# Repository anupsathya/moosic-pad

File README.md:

# moo-sic pad

A simple macro pad with 4 Cherry MX keys, a PEC-11R Rotary Encoder, a mini OLED screen and a vibration motor.

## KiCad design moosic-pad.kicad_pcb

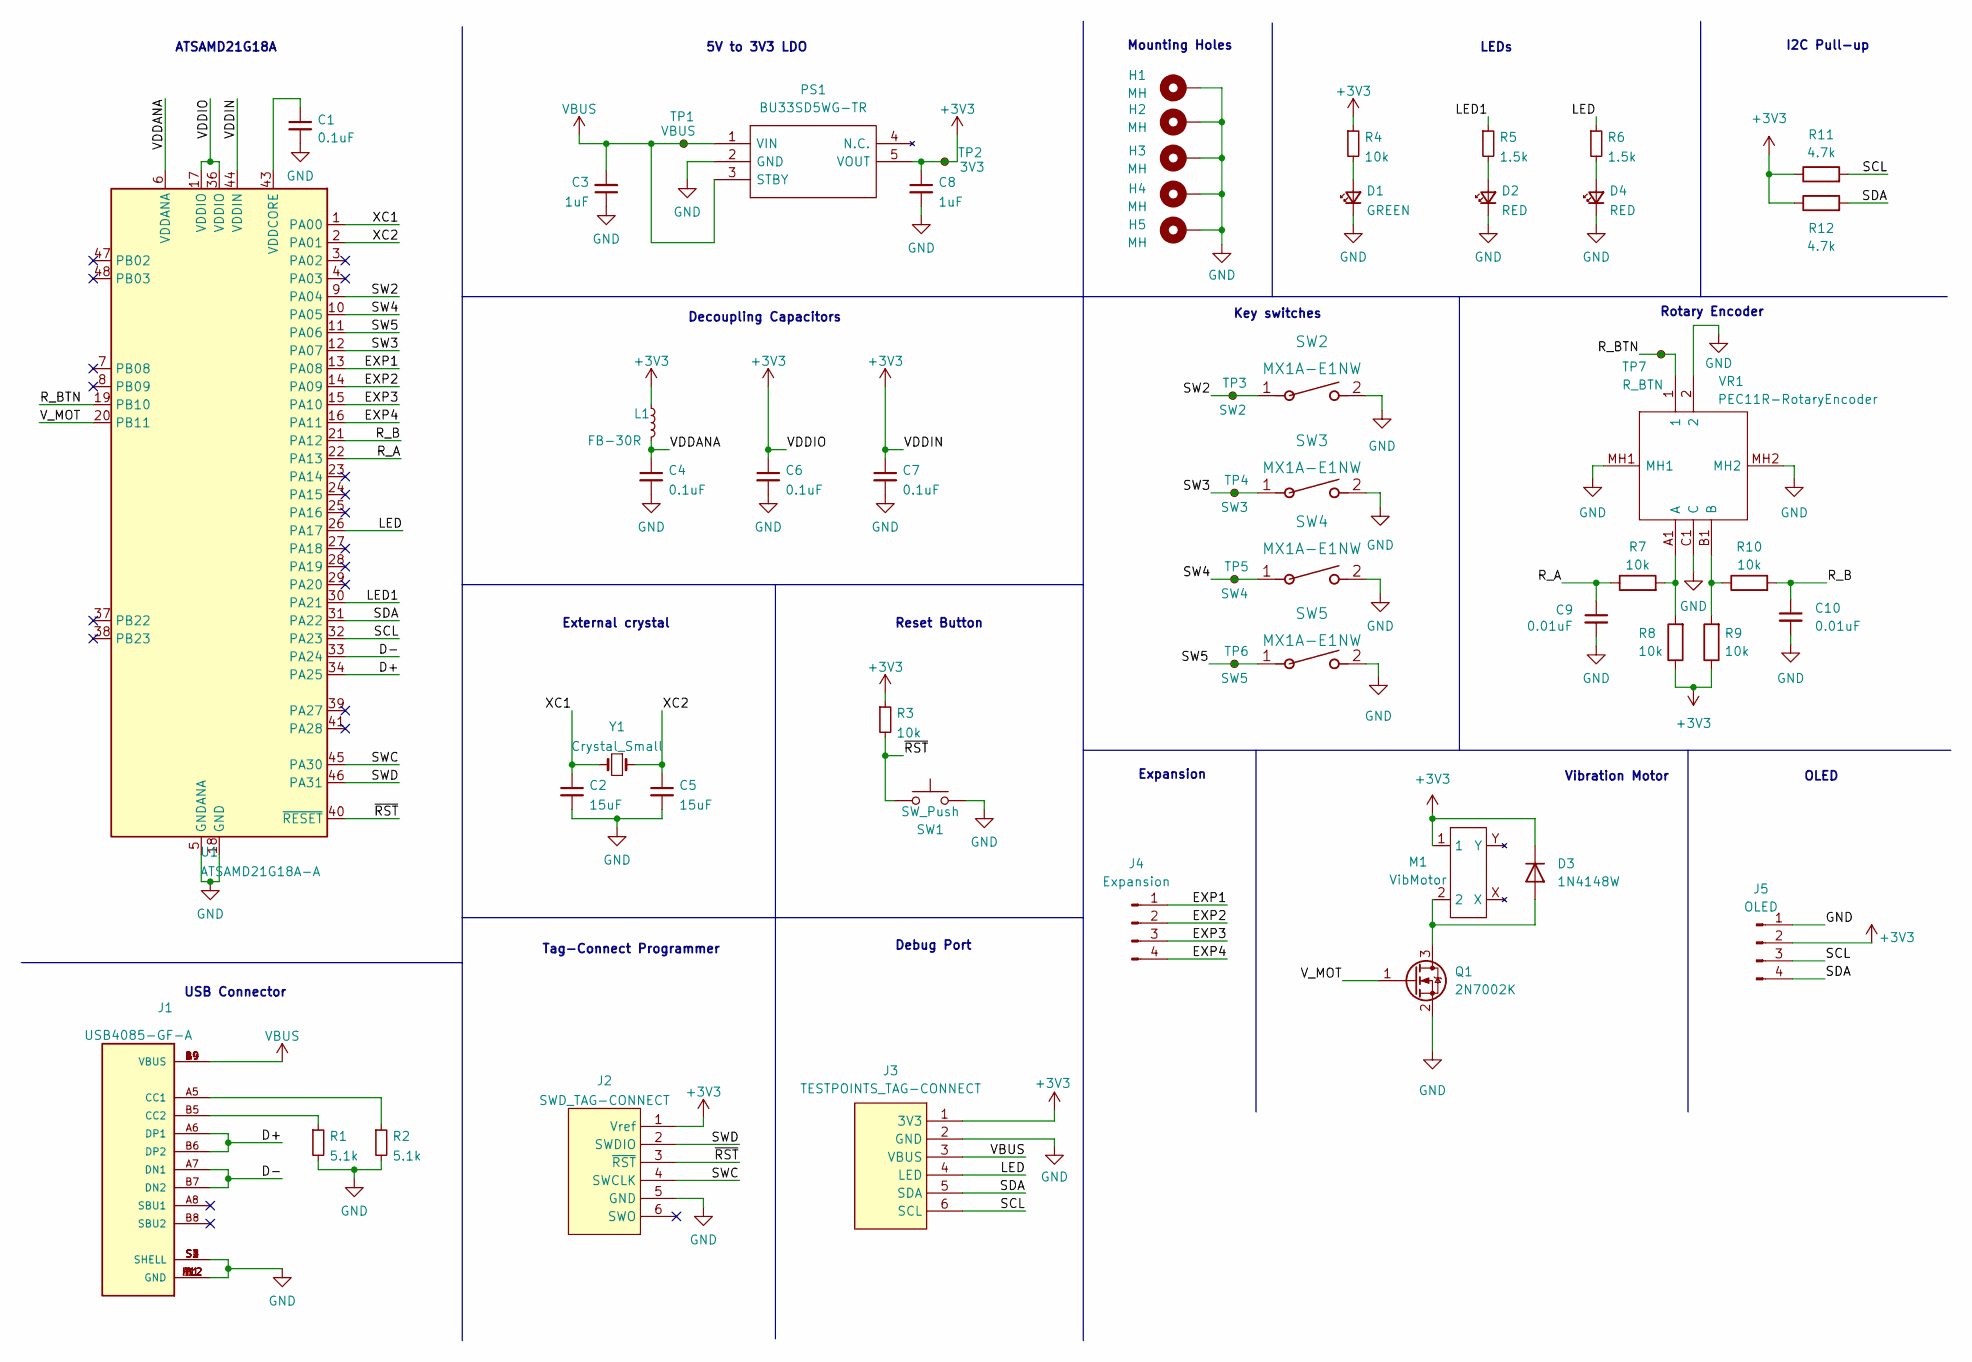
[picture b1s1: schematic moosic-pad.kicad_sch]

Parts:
C1, C4, C6, C7: 0.1uF; C_0603_1608Metric_Pad1.08x0.95mm_HandSolder
C2, C5: 15uF; C_0603_1608Metric_Pad1.08x0.95mm_HandSolder
C3, C8: 1uF; C_0603_1608Metric_Pad1.08x0.95mm_HandSolder
C9, C10: 0.01uF; C_0603_1608Metric_Pad1.08x0.95mm_HandSolder
D1: GREEN; LED_0603_1608Metric
D2, D4: RED; LED_0603_1608Metric
D3: 1N4148W; D_SOD-123
H1, H2, H3, H4, H5: MH; MountingHole_2.7mm_M2.5_DIN965_Pad
J1: USB4085-GF-A; GCT_USB4085-GF-A; PARTREV A4
J2: SWD_TAG-CONNECT; Tag-Connect_TC2030-IDC-FP_2x03_P1.27mm_Vertical
J3: TESTPOINTS_TAG-CONNECT; Tag-Connect_TC2030-IDC-NL_2x03_P1.27mm_Vertical
J4: Expansion; PinHeader_1x04_P1.00mm_Vertical
J5: OLED; PinHeader_1x04_P2.54mm_Vertical
L1: FB-30R; L_0603_1608Metric
M1: VibMotor; SeeedStudio_VibMotor
PS1: BU33SD5WG-TR; SOT95P280X125-5N; Mouser Part Number 755-BU33SD5WG-TR
Q1: 2N7002K; SOT-23
R1, R2: 5.1k; R_0603_1608Metric_Pad0.98x0.95mm_HandSolder
R3, R4, R7, R8, R9, R10: 10k; R_0603_1608Metric_Pad0.98x0.95mm_HandSolder
R5, R6: 1.5k; R_0603_1608Metric_Pad0.98x0.95mm_HandSolder
R11, R12: 4.7k; R_0603_1608Metric_Pad0.98x0.95mm_HandSolder
SW1: SW_Push; SW_SPST_TL3305A
SW2, SW3, SW4, SW5: MX1A-E1NW
TP1: VBUS; TestPoint_Pad_D1.0mm
TP2: 3V3; TestPoint_Pad_D1.0mm
TP3: SW2; TestPoint_Pad_D1.0mm
TP4: SW3; TestPoint_Pad_D1.0mm
TP5: SW4; TestPoint_Pad_D1.0mm
TP6: SW5; TestPoint_Pad_D1.0mm
TP7: R_BTN; TestPoint_Pad_D1.0mm
U1: ATSAMD21G18A-A; TQFP-48_7x7mm_P0.5mm
VR1: PEC11R-RotaryEncoder; PEC11R4220FS0024; Mouser Part Number 652-PEC11R-4220F-S24
Y1: Crystal_Small; Crystal_SMD_3215-2Pin_3.2x1.5mm

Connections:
+3V3: C6.1, C7.1, C8.1, D3.1 (K), J2.1 (Vref), J3.1 (3V3), J5.2, L1.1, M1.1, PS1.5 (VOUT), R3.1, R4.1, R8.1, R9.1, R11.1, R12.1, TP2.1, U1.17 (VDDIO), U1.36 (VDDIO), U1.44 (VDDIN)
/D+: J1.A6 (DP1), J1.B6 (DP2), U1.34 (PA25)
/D-: J1.A7 (DN1), J1.B7 (DN2), U1.33 (PA24)
/EXP1: J4.1, U1.13 (PA08)
/EXP2: J4.2, U1.14 (PA09)
/EXP3: J4.3, U1.15 (PA10)
/EXP4: J4.4, U1.16 (PA11)
/LED: J3.4 (LED), R6.1, U1.26 (PA17)
/LED1: R5.1, U1.30 (PA21)
/R_A: C9.1, R7.1, U1.22 (PA13)
/R_B: C10.1, R10.2, U1.21 (PA12)
/R_BTN: TP7.1, U1.19 (PB10), VR1.1
/SCL: J3.6 (SCL), J5.3, R11.2, U1.32 (PA23)
/SDA: J3.5 (SDA), J5.4, R12.2, U1.31 (PA22)
/SW2: SW2.1, TP3.1, U1.9 (PA04)
/SW3: SW3.1, TP4.1, U1.12 (PA07)
/SW4: SW4.1, TP5.1, U1.10 (PA05)
/SW5: SW5.1, TP6.1, U1.11 (PA06)
/SWC: J2.4 (SWCLK), U1.45 (PA30)
/SWD: J2.2 (SWDIO), U1.46 (PA31)
/VDDANA: C4.1, L1.2, U1.6 (VDDANA)
/V_MOT: Q1.1 (G), U1.20 (PB11)
/XC1: C2.1, U1.1 (PA00), Y1.2
/XC2: C5.1, U1.2 (PA01), Y1.1
/~RST: J2.3 (~RST), R3.2, SW1.1, U1.40 (~RESET)
GND: C1.2, C2.2, C3.1, C4.2, C5.2, C6.2, C7.2, C8.2, C9.2, C10.2, D1.1 (K), D2.1 (K), D4.1 (K), H1.1, H2.1, H3.1, H4.1, H5.1, J1.A1 (GND), J1.A12 (GND), J1.B1 (GND), J1.B12 (GND), J1.S1 (SHELL), J1.S2 (SHELL), J1.S3 (SHELL), J1.S4 (SHELL), J2.5 (GND), J3.2 (GND), J5.1, PS1.2 (GND), Q1.2 (S), R1.2, R2.2, SW1.2, SW2.2, SW3.2, SW4.2, SW5.2, U1.5 (GNDANA), U1.18 (GND), U1.35 (GND), U1.42 (GND), VR1.2, VR1.C1 (C), VR1.MH1, VR1.MH2
unnamed: C1.1, U1.43 (VDDCORE)
unnamed: D1.2 (A), R4.2
unnamed: D2.2 (A), R5.2
unnamed: D3.2 (A), M1.2, Q1.3 (D)
unnamed: D4.2 (A), R6.2
unnamed: J1.A5 (CC1), R2.1
unnamed: J1.B5 (CC2), R1.1
unnamed: R7.2, R8.2, VR1.A1 (A)
unnamed: R9.2, R10.1, VR1.B1 (B)
VBUS: C3.2, J1.A4 (VBUS), J1.A9 (VBUS), J1.B4 (VBUS), J1.B9 (VBUS), J3.3 (VBUS), PS1.1 (VIN), PS1.3 (STBY), TP1.1

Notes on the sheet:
I2C Pull-up
5V to 3V3 LDO
External crystal
Tag-Connect Programmer
Decoupling Capacitors
Mounting Holes
Vibration Motor
Key switches
Expansion
LEDs
Rotary Encoder
OLED
USB Connector
ATSAMD21G18A
Reset Button
Debug Port

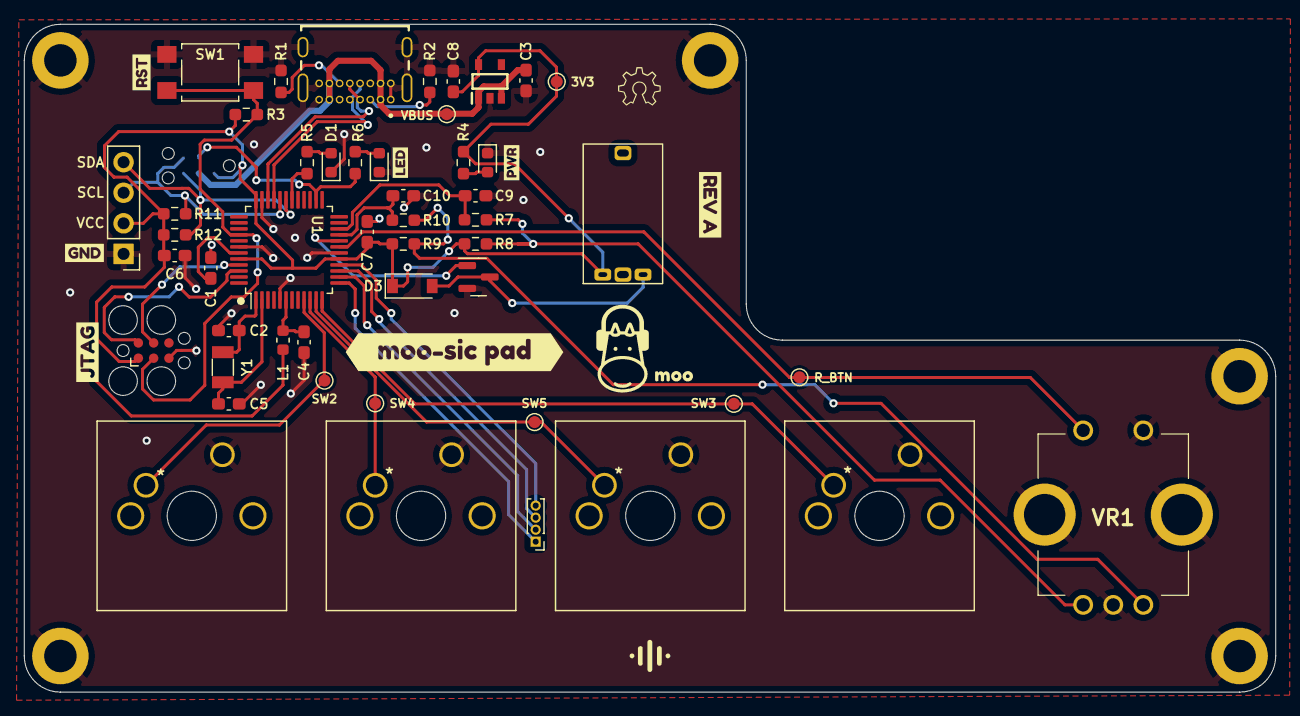
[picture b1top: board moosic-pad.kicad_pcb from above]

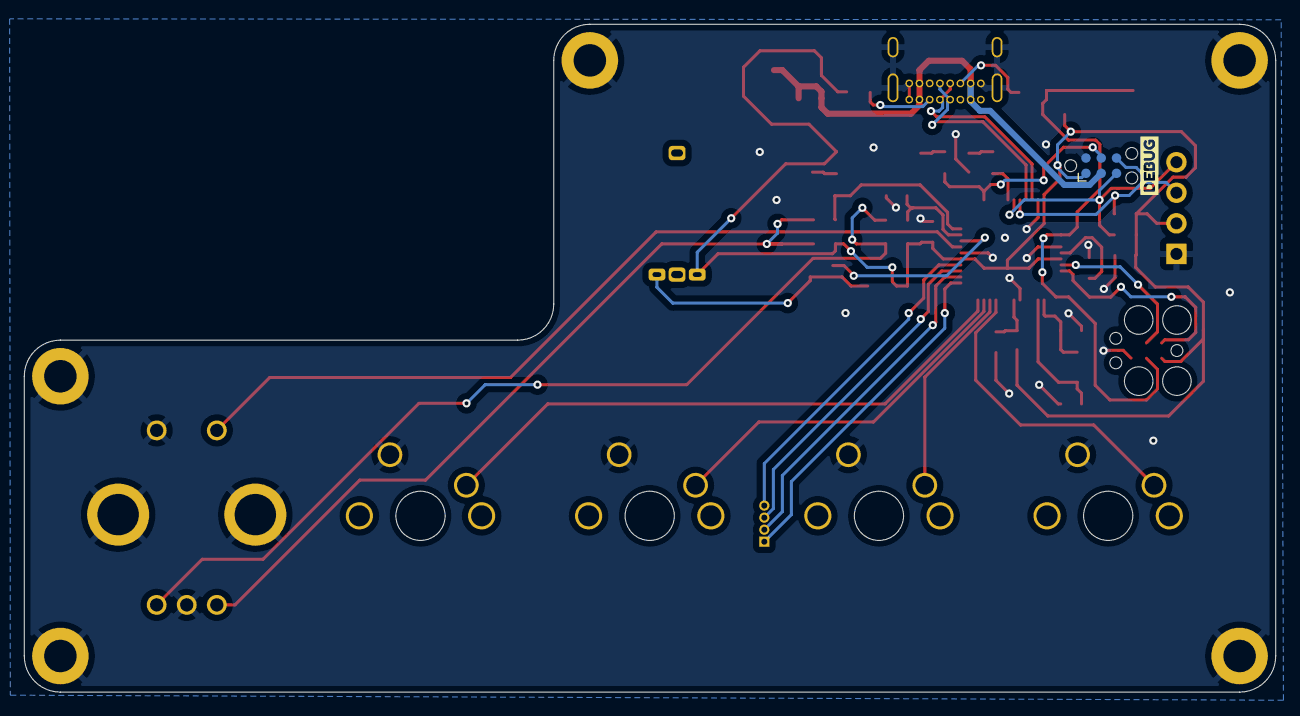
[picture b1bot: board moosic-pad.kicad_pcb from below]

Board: 2 copper layers, 104.0 x 55.5 mm, 64 parts (2 on the bottom side), 36 nets.

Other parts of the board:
kibuzzard-63E6A6CF: G***; kibuzzard-63E6A6CF
kibuzzard-63E48A56: G***; kibuzzard-63E48A56
kibuzzard-63E48CAF: G***; kibuzzard-63E48CAF
kibuzzard-63E48D19: G***; kibuzzard-63E48D19
kibuzzard-63E49FE3: G***; kibuzzard-63E49FE3
kibuzzard-63E52EE2: G***; kibuzzard-63E52EE2
kibuzzard-63E52F06: G***; kibuzzard-63E52F06
kibuzzard-63E579BA: G***; kibuzzard-63E579BA
kibuzzard-63E4897E: G***; kibuzzard-63E4897E

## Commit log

2023-04-27 init
2023-04-27 adding readme
2023-04-27 readme change
